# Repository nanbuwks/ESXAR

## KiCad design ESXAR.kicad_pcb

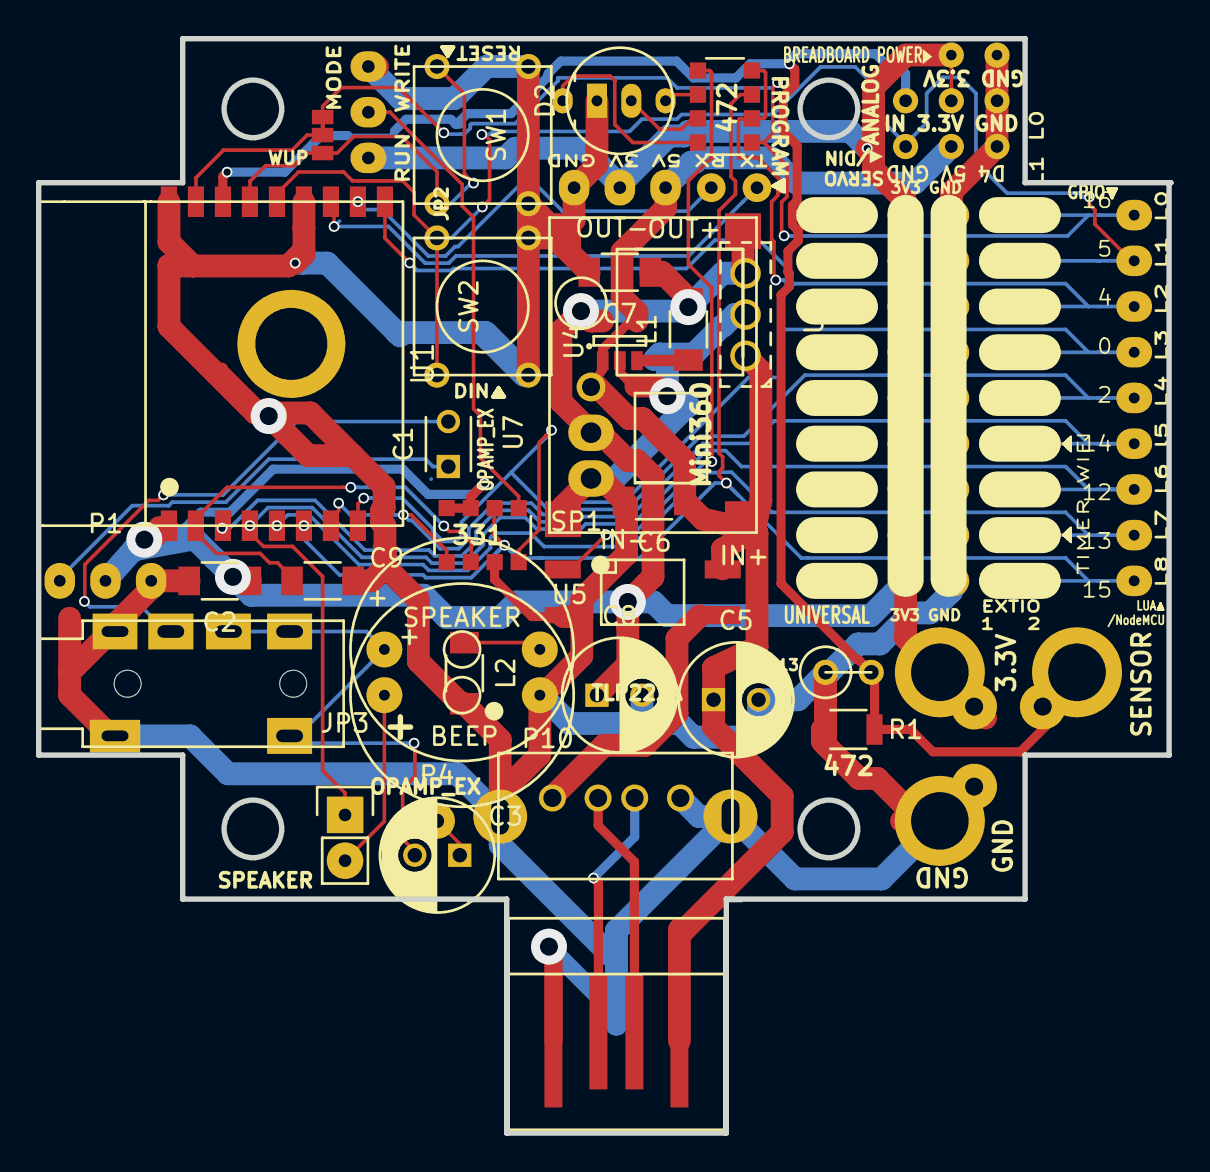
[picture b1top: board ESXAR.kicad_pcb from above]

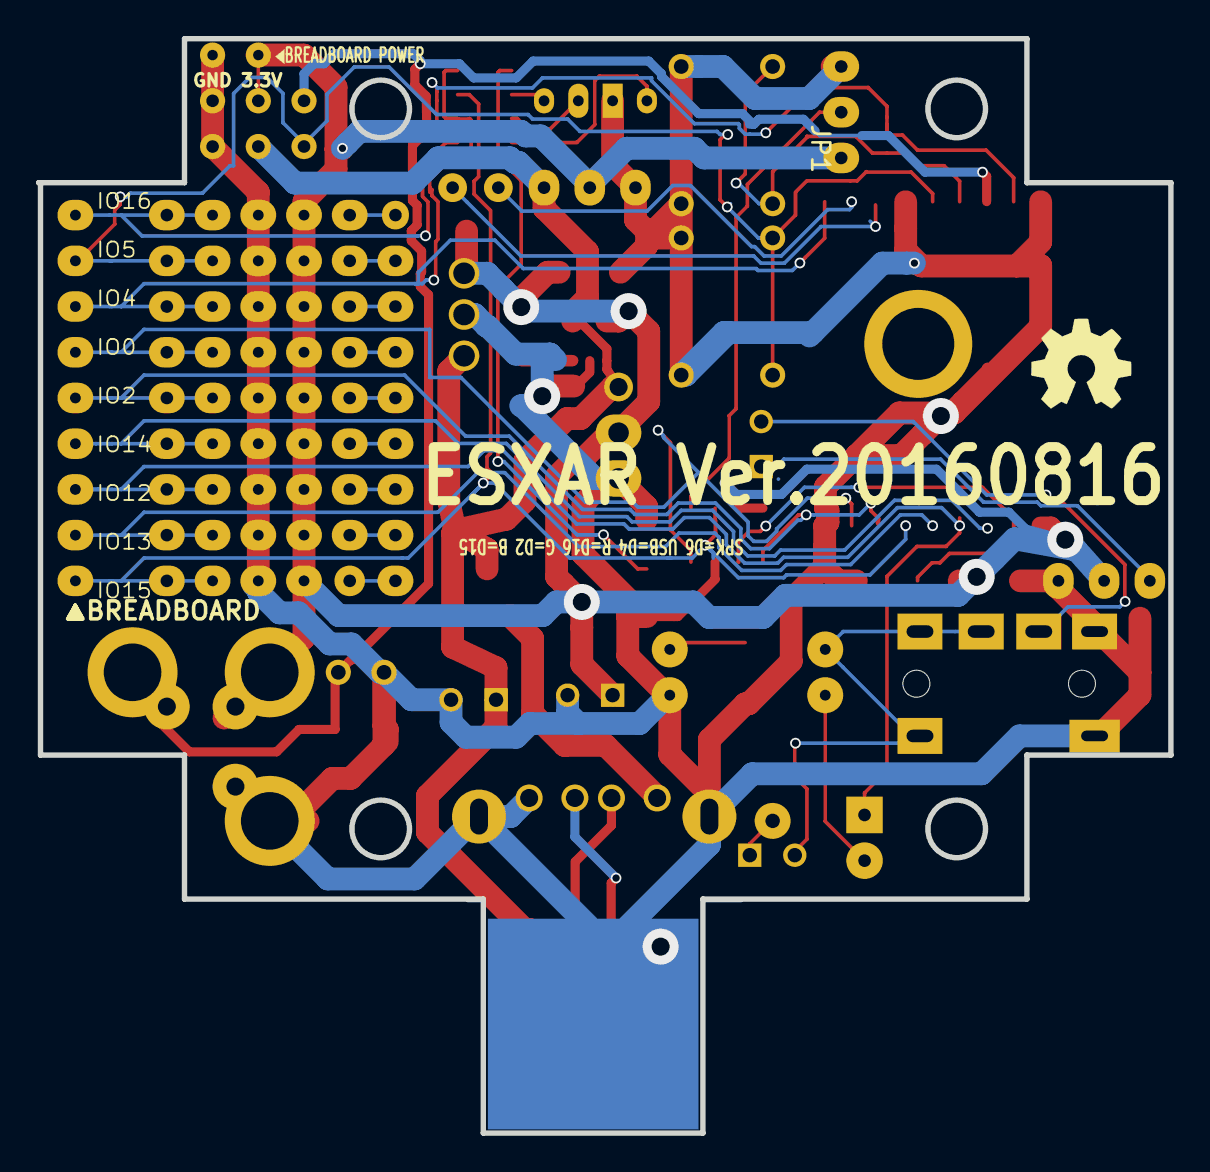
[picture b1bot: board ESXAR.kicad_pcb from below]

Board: 2 copper layers, 62.9 x 60.8 mm, 47 parts (4 on the bottom side), 40 nets.

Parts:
C1: 10uF; C_Disc_D3_P2.5
C2, C9: 0.1uF; C_1206_HandSoldering_Small
C3: CP; C_Radial_D6.3_L11.2_P2.5
C5, C8: 100uF; C_Radial_D6.3_L11.2_P2.5
C6, C7: 10uF; C_1206_HandSoldering_Small
D2: LED_RCBG; LED-RGB-5MM_Common_Cathode
JP1: MODE_JP; SolderWirePad_Oval_3xInline_0-65mmDrill
JP2: WAKEUP; Solder_Jumper_3
JP3: JUMPER; Pin_Header_Straight_1x02
L1: 4.7uH; C_1206_HandSoldering_Small
L2: L_Small; C_1206_HandSoldering_Small
OSHW: 1.1; OSHW_LOGL_SYLK_5mm
P1, P13: ANALOG; SolderWirePad_Oval_3xInline_0-65mmDrill
P2: BREADBOARD; SolderWirePad_Oval_9xInline_0-6mmDrill
P3: PROGRAM; SolderWirePad_Oval_5xInline_0-65mmDrill
P4: OPAMP EX; SolderWirePad_single_0-8mmDrill
P5: MODEJP; SolderWirePad_Oval_9xInline_0-6mmDrill
P6: VCCJP; SolderWirePad_Oval_9xInline_0-6mmDrill
P7: GNDJP; SolderWirePad_Oval_9xInline_0-6mmDrill
P8: SCREW; bornier3
P10: USB_A; USB_A_Vertical_Short
P11: USB_B; USB_A_Male_Board
P12: SERVO/INPUT; SolderWirePad_Oval_3xInline_0-65mmDrill
P16: BREADBOARD_POWER; Padmatrix-wide-02x01
P17: SENSOR; bornier3
P18: EXTIO; SolderWirePad_Oval_9xInline_0-7mmDrill
P19, P20: UNIVERSAL; SolderWirePad_Oval_9xInline_0-7mmDrill
R1: 4.7kΩ; R_1206
R13: 4.7kΩ; R1
RP1: R_PACK4; R_Array_Convex_4x1206
RP2: 4UNIT_R_PACK; R_Array_For_R_Multi_library_4x1206
SP1: SPEAKER; Buzzer_12x9.5RM7.6
SP2: BEEP; Buzzer_12x9.5RM7.6
SW1: RESET; SW_PUSH_SMALL
SW2: DIN; SW_PUSH_SMALL
U1: ESP-WROOM-02; ESP_WROOM_02
U3: AUDIO_JACK; 3_5mm_4P_phonejack_yizhijia_PJ313
U4: MT5201-3.3N; SOT-23-5
U5: TLP222A; Optocoupler_SMD_HandSoldering_KPC357_LTV35x_PC357_SingleCha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
U6: Mini360; Mini-360_DCDC_LM2596_module
U7: LD1117CV33; TO-220
U8: TA48M033F; SOT126_SOT32_Housing_Vertical_Mirrored

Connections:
+3V3: C2.1, C7.1, C8.1, JP1.3, L1.2, P1.2, P3.4, P6.1, P6.2, P6.3, P6.4, P6.5, P6.6, P6.7, P6.8, P6.9, P8.1, P13.2, P16.1, P17.1, RP2.5, RP2.7, U1.1, U4.5, U6.3, U7.3, U8.3
+5V: C5.1, C6.1, P3.3, P11.1, P12.2, U4.1, U4.4, U5.4, U6.1, U7.1, U8.1
GND: C2.2, C5.2, C6.2, C7.2, C8.2, C9.2, D2.2, JP1.1, L2.2, P1.3, P3.5, P7.1, P7.2, P7.3, P7.4, P7.5, P7.6, P7.7, P7.8, P7.9, P8.3, P10.4, P10.5, P11.4, P11.5, P12.3, P13.3, P16.2, P17.3, R1.1, R13.1, RP2.4, SP2.2, SW1.1, SW2.2, U1.9, U1.13, U1.18, U3.1, U4.2, U5.2, U6.2, U7.2, U8.2
unnamed: C1.1, P1.1
unnamed: C1.2, U3.4
unnamed: C3.1, P4.1
unnamed: C3.2, SP1.1, U3.2, U3.3
unnamed: C9.1, RP2.6, U1.2
unnamed: D2.1, RP1.8
unnamed: D2.3, RP1.7
unnamed: D2.4, RP1.6
unnamed: JP1.2, RP2.1
unnamed: JP2.1, SW1.2, U1.15
unnamed: JP2.2, JP2.3, P2.1, P5.1, P18.1, RP1.1, U1.17
unnamed: JP3.1, JP3.2, P2.7, P5.7, P18.7, SP2.1, U1.4
unnamed: L1.1, U4.3
unnamed: L2.1, SP1.2
unnamed: P3.1, U1.12
unnamed: P3.2, U1.11
unnamed: P10.1, U5.3
unnamed: P10.2, P11.2
unnamed: P10.3, P11.3
unnamed: P2.2, P5.2, P12.1, P18.2, SW2.1, U1.14
unnamed: P8.2, P13.1, P17.2, R1.2, R13.2, U1.16
unnamed: P2.3, P5.3, P18.3, RP1.2, RP1.4, U1.10
unnamed: P2.4, P5.4, P18.4, RP2.2, U1.8
unnamed: P2.5, P5.5, P18.5, RP2.8, U1.7
unnamed: P2.6, P5.6, P18.6, U1.3
unnamed: P2.8, P5.8, P18.8, U1.5
unnamed: P2.9, P5.9, P18.9, RP1.3, RP2.3, U1.6
unnamed: P19.1, P20.1
unnamed: P19.2, P20.2
unnamed: P19.3, P20.3
unnamed: P19.4, P20.4
unnamed: P19.5, P20.5
unnamed: P19.6, P20.6
unnamed: P19.7, P20.7
unnamed: P19.8, P20.8
unnamed: P19.9, P20.9
unnamed: RP1.5, U5.1

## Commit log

2016-07-29 first commit Ver20160715
2016-07-29 add documents
2016-07-29 add some documents
2016-08-02 Change IO Ext pin direction, and througehwole size.
2016-08-02 fix registor array bug
2016-08-03 Ver 20160802. add speaker jumper,change analog port layout, etc.
2016-08-05 Ver 20160804 Layout Change.
2016-08-16 Ver.20160805 change outline, rayout, delete opamp, etc...
2016-08-28 Ver.20170816 and documents
2016-08-29 documents fix
2016-10-04 Document update
2016-10-06 add doc/ESXARPoster.*
2016-12-09 some documents edited
